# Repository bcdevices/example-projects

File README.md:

# Example Projects

A collection of KiCad hardware design projects, well mostly KiCad.
Confiential files should not be placed here!

## Structure

Each project lives in its own folder:

```
example-projects/
├── board-name-1/
│   ├── board-name-1.kicad_pro
│   ├── board-name-1.kicad_pcb
│   ├── board-name-1.kicad_sch
│   └── bom.csv
└── board-name-2/
    └── ...
```

## Files

| Extension | Description |
|---|---|
| `.kicad_pro` | KiCad project file |
| `.kicad_pcb` | PCB layout |
| `.kicad_sch` | Schematic |
| `.csv` | Bill of materials |

## Requirements

- [KiCad](https://www.kicad.org) 7.0 or later

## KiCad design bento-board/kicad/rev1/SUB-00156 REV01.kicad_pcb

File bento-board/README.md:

# Bento Board

Open-source hardware sample board from Blue Clover Devices, used to
demonstrate PLT production test workflows. An RP2350B host MCU and an
ESP32-C3 wireless module sit alongside RGB LED, relay, sensor, buzzer,
QWIIC and MikroBUS sections, in an OKW IN-BOX form factor. The board
includes dedicated test points and Tag-Connect footprints for fixture-based test.

| Top | Bottom |
|---|---|
|  |  |

## Resources

- [PLT docs: Bento Board sample](https://docs.pltcloud.com/samples/board/bento/)
- [Bento PLT test plans](https://github.com/bcdevices/test-plans/tree/main/bento)
- [Bento Zephyr firmware](https://github.com/bcdevices/bento-zephyr-fw)

## Layout

```
bento-board/
├── kicad/              KiCad source projects (open the .kicad_pro)
│   ├── library/        Shared symbol + footprint library
│   ├── rev0/           SUB-00156 REV00
│   └── rev1/           SUB-00156 REV01
├── schematic/          Schematic exports (PDF, SVG), per revision
│   ├── rev0/
│   └── rev1/
├── layout/             Board renders and fabrication outputs, per revision
│   ├── rev0/
│   └── rev1/
├── firmware/           Prebuilt firmware images
│   └── blinky/
├── images/             Board photos
└── test/               PLT test plans
    └── flash-blinky/
```

Each `kicad/revN/` directory is a complete KiCad project; the schematic and
PCB must stay together for KiCad's project linking to work. `schematic/` and
`layout/` hold generated outputs only.

## Revisions

| Rev | Changes |
|---|---|
| REV00 | Initial release |
| REV01 | Tag-Connect footprint moved away from relay; added 4.7 µF capacitor |

## License

| Component | License |
|---|---|
| Hardware design files (KiCad) | [CERN-OHL-P-2.0](LICENSE-HARDWARE) |
| Firmware | Apache-2.0 ([firmware repo](https://github.com/bcdevices/example-projects/tree/main/bento-board/firmware/blinky)) |
| Documentation | [CC-BY-4.0](LICENSE-DOCS) |

## Credits

Derived from the Golioth Aludel Elixir (CERN-OHL-P-2.0), designed by
Chris Gammell, which itself descends from Jared Wolff's nRF9160 Feather.
Changes: RP2350B + ESP32-C3 architecture, OKW IN-BOX form factor,
sensor/relay/buzzer sections, and DFT test features.

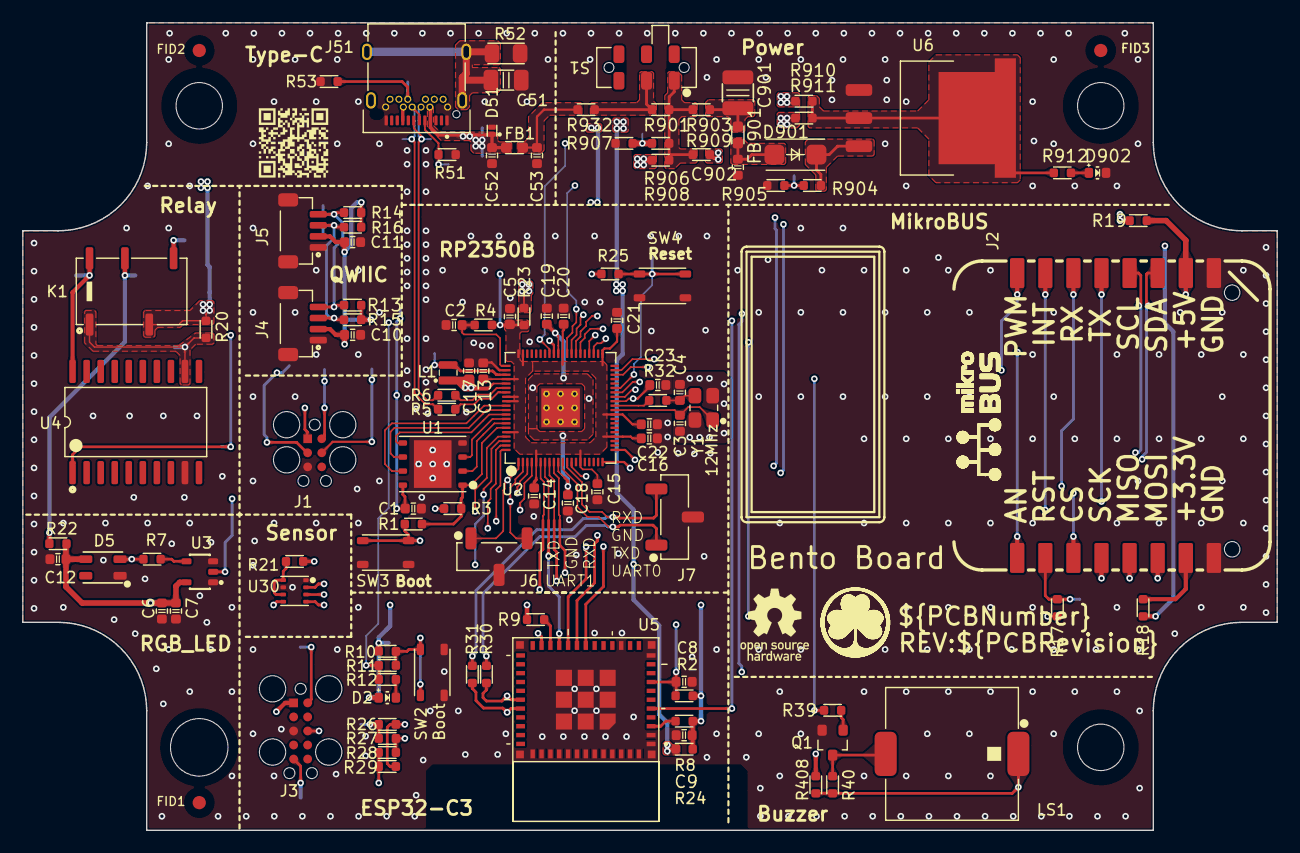
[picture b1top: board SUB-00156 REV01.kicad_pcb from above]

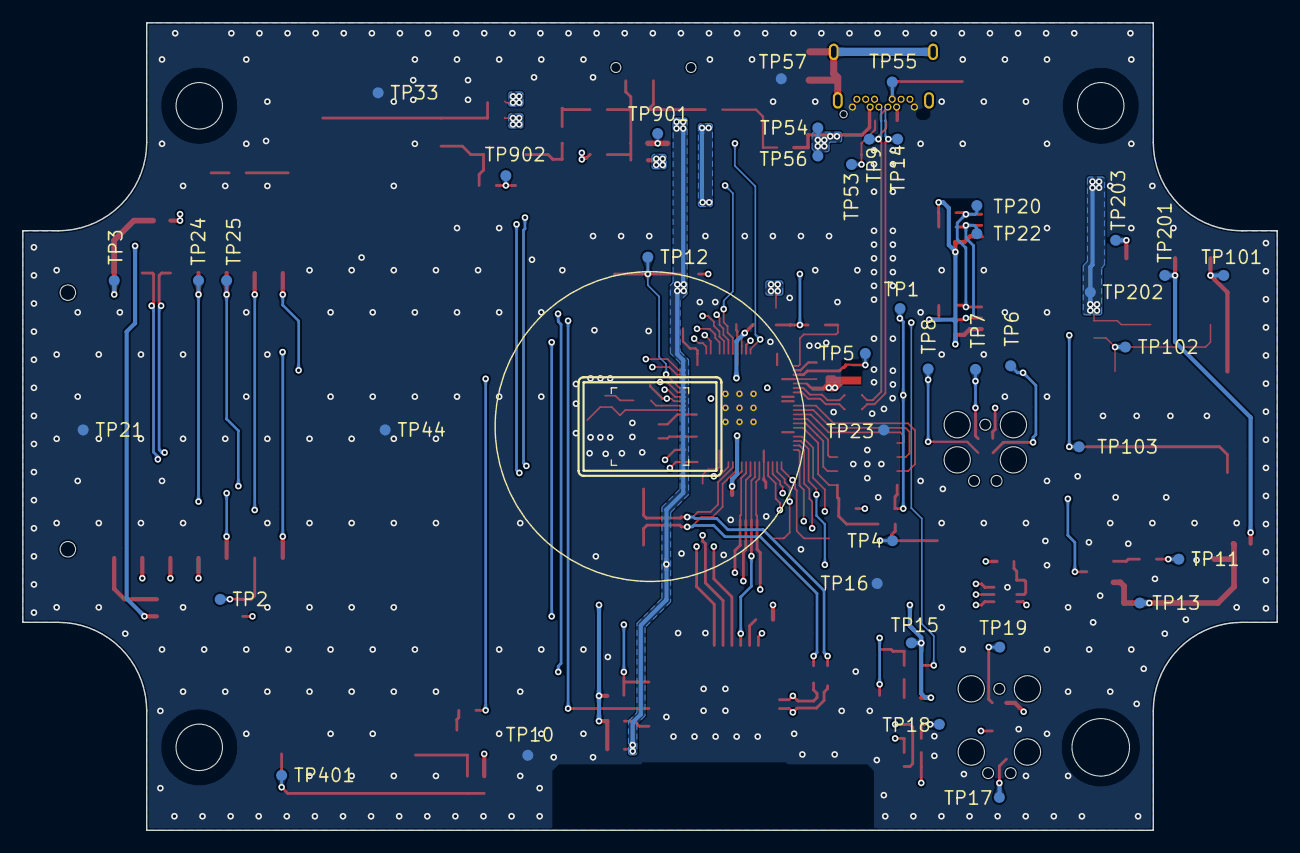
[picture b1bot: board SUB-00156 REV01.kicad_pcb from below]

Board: 4 copper layers, 113.4 x 73.0 mm, 163 parts (42 on the bottom side), 88 nets.

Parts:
C1, C7, C10, C11, C12, C14, C15, C18, C20, C21, C22, C23, C902: 0.1μF; CC0603-N
C2, C5, C9, C13, C16, C17, C19: 4.7μF; CC0603-N
C3, C4: 15pF; CC0603-N
C6, C8: 1µF; CC0603-N
C51: 100pF; CC1206-N
C52, C53: 100pF; CC0603-N
C901: 10µF; CC1210-N
D2, D902: LTST-C191KGKT; LED0603N-Green
D5: LTST-E683CEGBW; LTST-E683CEGBW-L
D51: SZESD7241N2T5G; 2-X2DFN (1x0.6)
D901: SK34A-LTP; SMA
FB1, FB901: 26Ohms@100 MHz; FB0603-N
FID1, FID2, FID3: Mark
J1: TC2030-MCP-NL; TC2030-IDC
J2: MIKROE-4319
J3: TC2050-IDC
J4, J5: BM04B-SRSS-TB(LF)(SN)
J6, J7: NPTC031KFXC-RC
J51: 10159872-00011LF
K1: 1462042-8
L1: 3.3µH; IND-201610_SMD-2N
LS1: PKLCS1212E4001-R1
Label1: Label 24*12; Laebl_24_12mm
Label2: Label 12*8; Laebl_12_8mmBlank
Lg1: OSHWA_Logo; OSHWA-Logo
Log1: Logo; LOGO_BCD_Product
MH1: MH_.204NPT
MH2, MH3, MH4: MH_.165NPT
PCB1: CMP-000451; PCB Part Number
Q1: MMBT3904-TP; SOT23
QR1: QR; BB_QR
R1: 2K; RC0603-N
R2, R9, R10, R12, R13, R14, R15, R16: 10K; RC0603-N
R3, R25, R904: 100K; RC0603-N
R4: 33R; RC0603-N
R5, R6: 27R; RC0603-N
R7: 1R; RC0603-N
R8, R11, R17, R18, R19, R20, R21, R22, R23, R24, R26, R27, R28, R29, R30, R31, R408, R901, R903, R908, R909, R910, R911, R932: 0R; RC0603-N
R32, R912: 1K; RC0603-N
R39: 4.7K; RC0603-N
R40: 470R; RC0603-N
R51, R53: 5.1K; RC0603-N
R52: 267K; RC1206-N
R905: 150K; RC0603-N
R906: 470K; RC0603-N
R907: 68K; RC0603-N
S1: JS202011JAQN
SW2, SW3, SW4: PTS810SJG250SMTRLFS; PTS810SJG250SMTR LFS
TP1: MCU_3V3; TP-SM-39MILC
TP2: TP2; TP-SM-39MILC
TP3: TP3; TP-SM-39MILC
TP4: TP4; TP-SM-39MILC
TP5: TP5; TP-SM-39MILC
TP6: MCU_RESET; TP-SM-39MILC
TP7: SWD_SWDIO; TP-SM-39MILC
TP8: SWD_SWCLK; TP-SM-39MILC
TP9: RP_USB_N; TP-SM-39MILC
TP10: TP10; TP-SM-39MILC
TP11: TP11; TP-SM-39MILC
TP12: TP12; TP-SM-39MILC
TP13: TP13; TP-SM-39MILC
TP14: RP_USB_P; TP-SM-39MILC
TP15: ESP32_3.3V; TP-SM-39MILC
TP16: ESP_GND; TP-SM-39MILC
TP17: ESP32_TX; TP-SM-39MILC
TP18: ESP32_RX; TP-SM-39MILC
TP19: ESP32-RST; TP-SM-39MILC
TP20: I2C_SCL; TP-SM-39MILC
TP21: TP21; TP-SM-39MILC
TP22: I2C_SDA; TP-SM-39MILC
TP23: MCU_GND; TP-SM-39MILC
TP24: SCI1_TXD; TP-SM-39MILC
TP25: SCI1_RXD; TP-SM-39MILC
TP33: TP33; TP-SM-39MILC
TP44: TP44; TP-SM-39MILC
TP53: TP53; TP-SM-39MILC
TP54: TP54; TP-SM-39MILC
TP55: TP55; TP-SM-39MILC
TP56: VBUS; TP-SM-39MILC
TP57: GND; TP-SM-39MILC
TP101: TP101; TP-SM-39MILC
TP102: TP102; TP-SM-39MILC
TP103: TP103; TP-SM-39MILC
TP201: TP201; TP-SM-39MILC
TP202: TP202; TP-SM-39MILC
TP203: TP203; TP-SM-39MILC
TP401: TP401; TP-SM-39MILC
TP901: TP901; TP-SM-39MILC
TP902: TP902; TP-SM-39MILC
U1: W25Q128JVPIQ; WSON127P6X5-8NP
U2: RP2350B; QFN040P10X10-80NPV
U3: SN74LVC1G125DBVR; SOT23-5
U4: ULN2803CDWR; SOIC127P10.3X2.65-20N
U5: ESP32-C3-MINI-1-N4X; ESP32-C3-MINI-1-N4
U6: LM1086ISX-3.3/NOPB; TO-263
U30: BME280; LGA065P2.5X2.5-8N
Y1: 12 MHz; OSC3.2X2.5-4N

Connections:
/+3.3V: R21.1, R23.1, R24.1, R408.1, R911.2
/+5V: K1.3, R20.2, R908.2, TP202.1 (TP_1)
/Addr RGB LED/LED_DIN: D5.2 (DIN), R7.2, TP11.1 (TP_1)
/Addr RGB LED/LED_OUT: R7.1, U3.4 (Y)
/Addr RGB LED/RGB_5V: C6.2, C7.1, C12.1, D5.4 (VDD), R22.2, TP13.1 (TP_1), U3.5 (VCC)
/Addr RGB LED/RGB_5V_IN: K1.7, R22.1, TP201.1 (TP_1)
/Buzzer/AUDIO_EN: Q1.1 (B), R39.2
/Buzzer/BUZZER_VSYS: LS1.1, R40.1, R408.2, TP401.1 (TP_1)
/Buzzer/Buzzer-: LS1.2, Q1.3 (C), R40.2
/ESP32-C3 RFSoC/BOOT: R10.2, R11.1, SW2.3, SW2.4, U5.23 (IO9)
/ESP32-C3 RFSoC/C3_SPI.MISO: U2.77 (GPIO0), U5.19 (IO5)
/ESP32-C3 RFSoC/C3_SPI.MOSI: U2.80 (GPIO3), U5.18 (IO4)
/ESP32-C3 RFSoC/C3_SPI.SCK: U2.79 (GPIO2), U5.20 (IO6)
/ESP32-C3 RFSoC/ESP32_3.3V: C9.1, D2.1 (A), J3.1, R2.1, R8.2, R9.2, R10.1, R24.2, TP15.1 (TP_1)
/ESP32-C3 RFSoC/ESP32_RST: C8.1, J3.10, R2.2, TP19.1 (TP_1), U2.48 (GPIO39), U5.8 (EN)
/ESP32-C3 RFSoC/ESP32_RX: J3.8, R26.1, R27.1, TP18.1 (TP_1)
/ESP32-C3 RFSoC/ESP32_RXD0: R26.2, R29.2, R30.2, U5.30 (RXD0)
/ESP32-C3 RFSoC/ESP32_TX: J3.5, R28.1, R29.1, TP17.1 (TP_1)
/ESP32-C3 RFSoC/ESP32_TXD0: R27.2, R28.2, R31.2, U5.31 (TXD0)
/ESP32-C3 RFSoC/IO_STRAP: R9.1, U5.22 (IO8)
/ESP32-C3 RFSoC/PWR_FLAG: R8.1, U5.3 (3V3)
/Power/OUT_3V3_EXT: C10.1, C11.1, J4.2, J5.2, R13.1, R14.1, R15.1, R16.1, R18.1, R910.2
/Power/VBUS4V65: D901.2, R904.1, U6.3 (IN)
/Power/VBUS5V: C902.1, D901.1, FB901.2
/Power/VBUSPower: R901.2, R903.1, R906.1, R908.1, R909.1, S1.1
/Power/VBUSVCC: R901.1, R932.2, S1.2
/Power/VBUSVdd: C901.1, FB901.1, R903.2
/Power/VBUS_IN: C53.1, FB1.2, R932.1
/Power/VREG_3V3: R910.1, R911.1, R912.1, U6.2 (OUT), U6.4 (TAB)
/Qwiic/SENS_I2C.SCL: J2.12 (SCL), J4.4, J5.4, R13.2, R14.2, TP20.1 (TP_1), U2.21 (GPIO21)
/Qwiic/SENS_I2C.SDA: J2.11 (SDA), J4.3, J5.3, R15.2, R16.2, TP22.1 (TP_1), U2.20 (GPIO20)
/RP2350 MCU/ADC0: R904.2, R905.1, TP902.1 (TP_1), U2.49 (GPIO40/ADC0)
/RP2350 MCU/ADC1: J2.1 (AN), U2.52 (GPIO41/ADC1)
/RP2350 MCU/ADC2: R906.2, R907.1, TP901.1 (TP_1), U2.53 (GPIO42/ADC2)
/RP2350 MCU/AVDD: C2.1, R4.1, U2.61 (VREG_AVDD)
/RP2350 MCU/BootSet: R1.2, SW3.1, SW3.2, TP4.1 (TP_1)
/RP2350 MCU/MCU_3V3: C1.1, C5.1, C13.1, C14.1, C15.1, C16.1, C20.1, C21.1, C22.1, J1.1, R3.1, R4.2, R23.2, R25.2, TP1.1 (TP_1), U1.8 (VCC), U2.5 (IOVDD), U2.15 (IOVDD), U2.24 (IOVDD), U2.29 (IOVDD), U2.41 (IOVDD), U2.50 (IOVDD), U2.59 (ADC_AVDD), U2.60 (IOVDD), U2.64 (VREG_VIN), U2.68 (USB_OTP_VDD), U2.69 (QSPI_IOVDD), U2.76 (IOVDD)
/RP2350 MCU/MCU_RESET: J1.3, R25.1, SW4.3, SW4.4, TP6.1 (TP_1), TP12.1 (TP_1), U2.35 (RUN)
/RP2350 MCU/QSPI_SCLK: U1.6 (CLK), U2.71 (QSPI_SCLK)
/RP2350 MCU/QSPI_SD0: U1.5 (DI_IO0), U2.72 (QSPI_D0)
/RP2350 MCU/QSPI_SD1: U1.2 (DO_IO1), U2.74 (QSPI_SD1)
/RP2350 MCU/QSPI_SD2: U1.3 (~WP_IO2), U2.73 (QSPI_SD2)
/RP2350 MCU/QSPI_SD3: U1.7 (~HOLD_IO3), U2.70 (QSPI_SD3)
/RP2350 MCU/QSPI_SS0: R1.1, R3.2, U1.1 (~CS), U2.75 (QSPI_SS)
/RP2350 MCU/RP_PWM0: R39.1, U2.38 (GPIO30)
/RP2350 MCU/RP_PWM1: J2.16 (PWM), U2.39 (GPIO31)
/RP2350 MCU/RP_S0: R17.1, U2.43 (GPIO34)
/RP2350 MCU/RP_S1: TP103.1 (TP_1), U2.44 (GPIO35), U4.1 (1B)
/RP2350 MCU/RP_S2: U2.13 (GPIO14), U3.2 (A)
/RP2350 MCU/RP_S3: R11.2, R12.2, U2.46 (GPIO37)
/RP2350 MCU/RP_S4: U2.47 (GPIO38), U5.5 (IO2)
/RP2350 MCU/RSPI0_SSL0: U2.78 (GPIO1), U30.2 (CSB)
/RP2350 MCU/SCI1_CST: J2.15 (INT), U2.4 (GPIO7)
/RP2350 MCU/SCI1_RTS: J2.3 (CS), U2.3 (GPIO6)
/RP2350 MCU/SCI1_RXD: J2.13 (TX), J6.3, TP24.1 (TP_1), U2.2 (GPIO5)
/RP2350 MCU/SCI1_TXD: J2.14 (RX), J6.1, TP25.1 (TP_1), U2.1 (GPIO4)
/RP2350 MCU/SCI3_RXD: J7.3, R31.1, U2.12 (GPIO13)
/RP2350 MCU/SCI3_TXD: J7.1, R30.1, U2.11 (GPIO12)
/RP2350 MCU/SENS_SPI.MISO: J2.5 (MISO), U2.6 (GPIO8), U30.5 (SDO)
/RP2350 MCU/SENS_SPI.MOSI: J2.6 (MOSI), U2.9 (GPIO11), U30.3 (SDI)
/RP2350 MCU/SENS_SPI.SCK: J2.4 (SCK), U2.8 (GPIO10), U30.4 (SCK)
/RP2350 MCU/SPIS_SS: U2.7 (GPIO9), U5.21 (IO7)
/RP2350 MCU/SWD_SWCLK: J1.4, TP8.1 (TP_1), U2.33 (SWCLK)
/RP2350 MCU/SWD_SWDIO: J1.2, TP7.1 (TP_1), U2.34 (SWDIO)
/RP2350 MCU/USB_N: R6.2, U2.66 (USB_D-)
/RP2350 MCU/USB_P: R5.2, U2.67 (USB_D+)
/RP2350 MCU/VREG_FB: C17.1, C18.1, C19.1, C23.1, L1.1, U2.10 (DVDD), U2.32 (DVDD), U2.51 (DVDD), U2.65 (VREG_FB)
/RP2350 MCU/VREG_LX: L1.2, TP5.1 (TP_1), U2.63 (VREG_LX)
/RP2350 MCU/XIN: C3.1, U2.30 (XIN), Y1.1
/RP2350 MCU/XOUT: R32.2, U2.31 (XOUT)
/RP2350 MCU/XR: C4.1, R32.1, Y1.3
/Relay/COIL_N: K1.8, TP101.1 (TP_1), U4.20 (1C)
/Relay/K_NO: K1.5, TP203.1 (TP_1)
/Relay/VSYS_5V: K1.1, R20.1, TP102.1 (TP_1), U4.12 (COM)
/Sensor/VSYS_3V3: R21.2, U30.6 (VDDIO), U30.8 (VDD)
/Type-C/CC1: J51.A5 (CC1), R51.1, TP53.1 (TP_1)
/Type-C/CC2: J51.B5 (CC2), R53.1, TP55.1 (TP_1)
/Type-C/RP_USB_N: J51.A7 (DN1), J51.B7 (DN2), R6.1, TP9.1 (TP_1)
/Type-C/RP_USB_P: J51.A6 (DP1), J51.B6 (DP2), R5.1, TP14.1 (TP_1)
/Type-C/Shield: C51.1, J51.SH (Shield), R52.1
/Type-C/VBUS: C52.1, D51.1, FB1.1, J51.A4 (VBUS), J51.A9 (VBUS), J51.B4 (VBUS), J51.B9 (VBUS), TP54.1 (TP_1), TP56.1 (TP_1)
/mikroBUS/MIKRO_3V3: J2.7 (3.3V), R18.2
/mikroBUS/MIKRO_5V: J2.10 (5V), R19.1, TP3.1 (TP_1)
/mikroBUS/MIKRO_5V_IN: R19.2, R909.2
/mikroBUS/RTS: J2.2 (RST), R17.2, TP2.1 (TP_1)
GND: C1.2, C2.2, C3.2, C4.2, C5.2, C6.1, C7.2, C8.2, C9.2, C10.2, C11.2, C12.2, C13.2, C14.2, C15.2, C16.2, C17.2, C18.2, C19.2, C20.2, C21.2, C22.2, C23.2, C51.2, C52.2, C53.2, C901.2, C902.2, D5.1 (VSS), D51.2, D902.2 (K), J1.5, J2.8 (GND), J2.9 (GND), J3.3, J4.1, J4.SH1, J4.SH2, J5.1, J5.SH1, J5.SH2, J6.2, J7.2, J51.A1 (GND), J51.A12 (GND), J51.B1 (GND), J51.B12 (GND), Q1.2 (E), R51.2, R52.2, R53.2, R905.2, R907.2, SW2.1, SW2.2, SW3.3, SW3.4, SW4.1, SW4.2, TP10.1 (TP_1), TP16.1 (TP_1), TP21.1 (TP_1), TP23.1 (TP_1), TP33.1 (TP_1), TP44.1 (TP_1), TP57.1 (TP_1), U1.4 (GND), U1.9 (Pad), U2.62 (VREG_PGND), U2.81 (PadGnd), U3.1 (~OE), U3.3 (GND), U4.9 (GND), U5.1 (GND), U5.2 (GND), U5.11 (GND), U5.14 (GND), U5.36 (GND), U5.37 (GND), U5.38 (GND), U5.39 (GND), U5.40 (GND), U5.41 (GND), U5.42 (GND), U5.43 (GND), U5.44 (GND), U5.45 (GND), U5.46 (GND), U5.47 (GND), U5.48 (GND), U5.49 (GND), U5.50 (GND), U5.51 (GND), U5.52 (GND), U5.53 (GND), U6.1 (ADJ), U30.1 (GND), U30.7 (GND), Y1.2, Y1.4
unnamed: D2.2 (K), R12.1
unnamed: D902.1 (A), R912.2

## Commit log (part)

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2026-04-15 Remove incorrectly nested repos
2026-04-15 Remove .DS_Store
2026-04-15 Add initial example projects
2026-04-16 emphasized not to put confidential stuff here.
    Clarified project description and added confidentiality note.
2026-04-16 Add example project files
2026-04-24 Add Bento Board 2 REV00 KiCad source files
2026-04-24 Flatten directory structure
2026-05-07 Add bento blinky flashing test plans.
2026-05-07 Remove .DS_Stores
2026-05-07 Add blinky Zephyr programs for bento1 + 2.
    Note that currently the bento2 example is the same as bento1
2026-05-07 Blinky.hex is the filename now
2026-05-07 added svg files for pcb and schem
2026-05-08 Update example test plans
